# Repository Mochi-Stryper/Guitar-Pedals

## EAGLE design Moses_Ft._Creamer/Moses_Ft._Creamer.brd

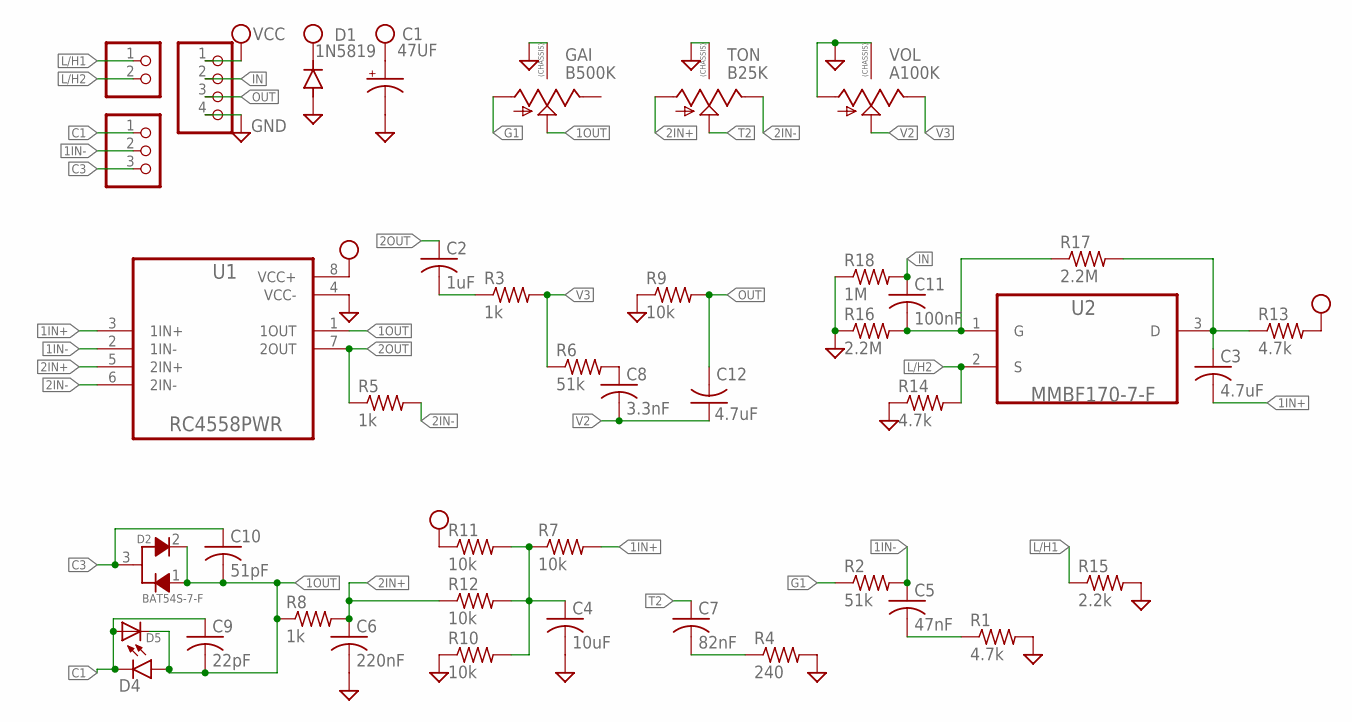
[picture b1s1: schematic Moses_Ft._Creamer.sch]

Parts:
C1: 47UF; PAN_B_SMD+THRU
C2: 1uF; C0805
C3, C12: 4.7uF; C1206
C4: 10uF; C1206
C5: 47nF; C0603
C6: 220nF; C0603
C7: 82nF; C0603
C8: 3.3nF; C0603
C9: 22pF; C0603
C10: 51pF; C0603
C11: 100nF; C0603
D1: 1N5819; SOD123
D2: BAT54S-7-F; SOT23-3
D4: LED0603; LED-0603
D5: DIODESOD-123; SOD-123
GAI: B500K; 9MM_SNAP-IN_POT
JP1: PINHD-1X4; 1X04
JP2: PINHD-1X2; 1X02
JP3: PINHD-1X3; 1X03
R1, R13, R14: 4.7k; R0603
R2, R6: 51k; R0603
R3, R5, R8: 1k; R0603
R4: 240; R0603
R7, R9, R10, R11, R12: 10k; R0603
R15: 2.2k; R0603
R16, R17: 2.2M; R0603
R18: 1M; R0603
TON: B25K; 9MM_SNAP-IN_POT
U1: RC4558PWR; SOP65P640X120-8N
U2: MMBF170-7-F; SOT103P240X110-3N
VOL: A100K; 9MM_SNAP-IN_POT

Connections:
1IN+: C3.2, R7.2, U1.3 (1IN+)
1IN-: C5.1, JP3.2, R2.2, U1.2 (1IN-)
1OUT: C9.2, C10.2, D2.1, D2.2, D4.A, D5.C, GAI.2 (S), R8.1, U1.1 (1OUT)
2IN+: C6.1, R8.2, R12.1, TON.1 (A), U1.5 (2IN+)
2IN-: R5.2, TON.3 (E), U1.6 (2IN-)
2OUT: C2.1, R5.1, U1.7 (2OUT)
C1: C9.1, D4.C, D5.A, JP3.1
C3: C10.1, D2.3, JP3.3
G1: GAI.1 (A), R2.1
GND: C1.-, C1.-- (-), C4.2, C6.2, D1.A, GAI.CHASSIS1, GAI.CHASSIS2, JP1.4, R1.2, R4.2, R9.1, R10.1, R14.1, R15.2, R16.1, R18.1, TON.CHASSIS1, TON.CHASSIS2, U1.4 (VCC-), VOL.1 (A), VOL.CHASSIS1, VOL.CHASSIS2
IN: C11.1, JP1.2, R18.2
L/H1: JP2.1, R15.1
L/H2: JP2.2, R14.2, U2.2 (S)
unnamed: C11.2, R16.2, R17.1, U2.1 (G)
unnamed: C3.1, R13.1, R17.2, U2.3 (D)
unnamed: C5.2, R1.1
unnamed: C4.1, R7.1, R10.2, R11.2, R12.2
unnamed: C2.2, R3.1
unnamed: C7.2, R4.1
unnamed: C8.1, R6.2
OUT: C12.2, JP1.3, R9.2
T2: C7.1, TON.2 (S)
V2: C8.2, C12.1, VOL.2 (S)
V3: R3.2, R6.1, VOL.3 (E)
VCC: C1.+, C1.++ (+), D1.C, JP1.1, R11.1, R13.2, U1.8 (VCC+)

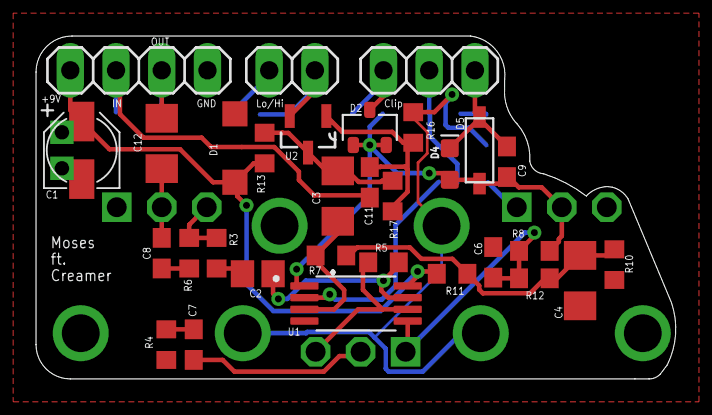
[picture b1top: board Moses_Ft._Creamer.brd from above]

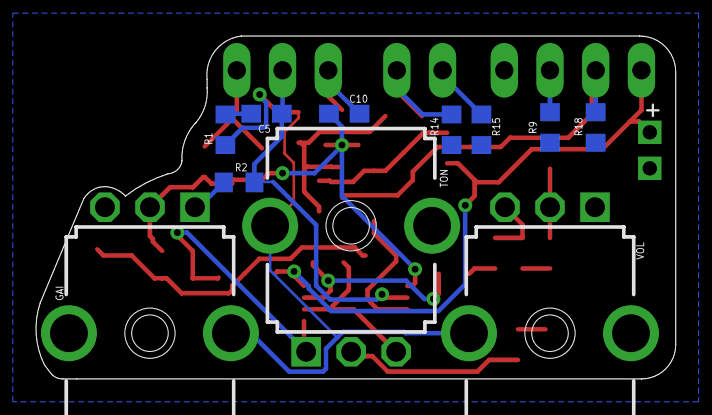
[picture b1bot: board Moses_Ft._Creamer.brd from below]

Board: 2 copper layers, 35.5 x 19.1 mm, 42 parts (11 on the bottom side), 25 nets.

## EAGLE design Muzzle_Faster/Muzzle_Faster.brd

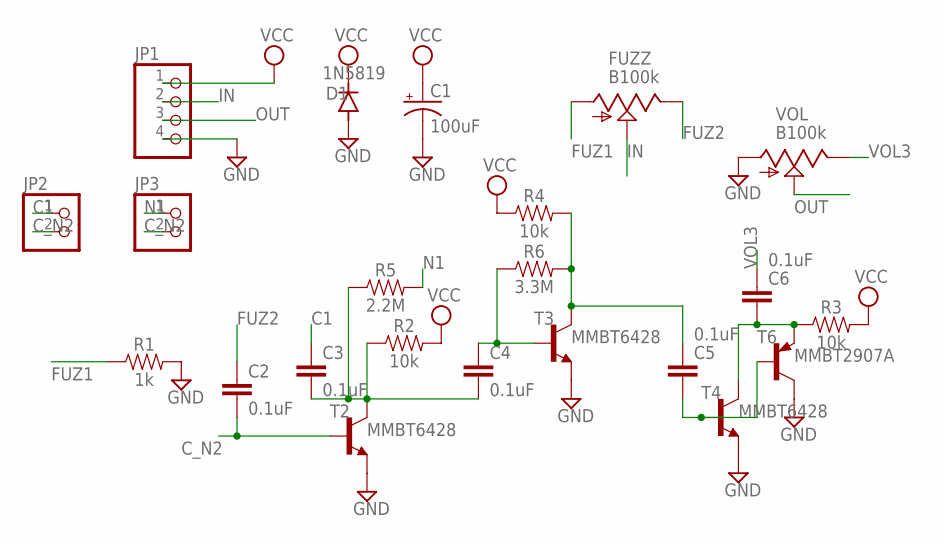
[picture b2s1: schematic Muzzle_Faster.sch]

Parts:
C1: 100uF; PAN_B_SMD+THRU
C2, C3, C4, C5, C6: 0.1uF; 0603
D1: 1N5819; SOD123
FUZZ: B100k; 9MM_SNAP-IN_POT
JP1: PINHD-1X4; 1X04
JP2, JP3: PINHD-1X2; 1X02
R1: 1k; 0603
R2, R3, R4: 10k; 0603
R5: 2.2M; 0603
R6: 3.3M; 0603
T2, T3, T4: MMBT6428; SOT23-BEC
T6: MMBT2907A; SOT23-BEC
VOL: B100k; 9MM_SNAP-IN_POT

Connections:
C1: C3.1, JP2.1
C_N2: C2.2, JP2.2, JP3.2, T2.B
FUZ1: FUZZ.1 (A), R1.1
FUZ2: C2.1, FUZZ.3 (E)
GND: C1.-, C1.-- (-), D1.A, JP1.4, R1.2, T2.E, T3.E, T4.E, T6.C, VOL.1 (A)
IN: FUZZ.2 (S), JP1.2
N1: JP3.1, R5.2
unnamed: C3.2, C4.2, R2.1, R5.1, T2.C
unnamed: C4.1, R6.1, T3.B
unnamed: C5.1, R4.2, R6.2, T3.C
unnamed: C5.2, T4.B, T6.B
unnamed: C6.2, R3.1, T4.C, T6.E
OUT: JP1.3, VOL.2 (S)
VCC: C1.+, C1.++ (+), D1.C, JP1.1, R2.2, R3.2, R4.1
VOL3: C6.1, VOL.3 (E)

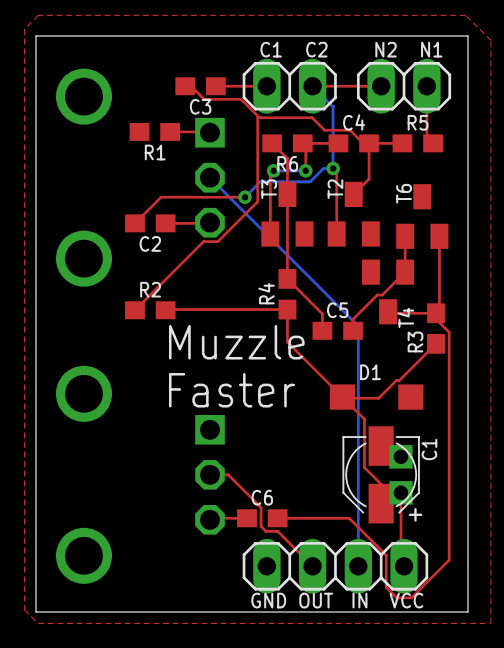
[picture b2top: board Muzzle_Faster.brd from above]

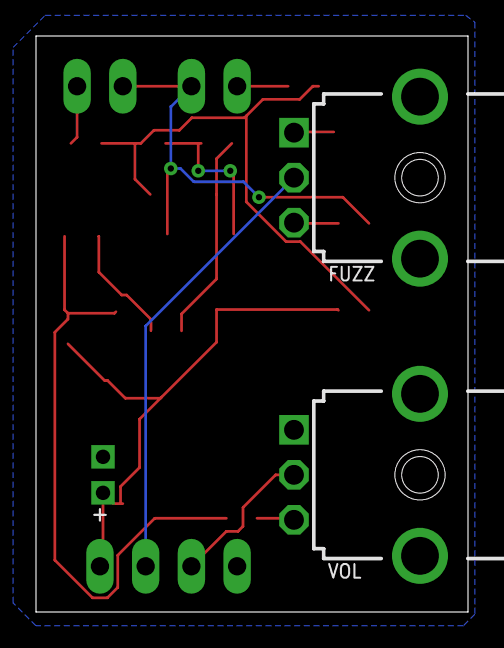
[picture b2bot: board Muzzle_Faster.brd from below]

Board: 2 copper layers, 24.0 x 32.0 mm, 22 parts (2 on the bottom side), 15 nets.

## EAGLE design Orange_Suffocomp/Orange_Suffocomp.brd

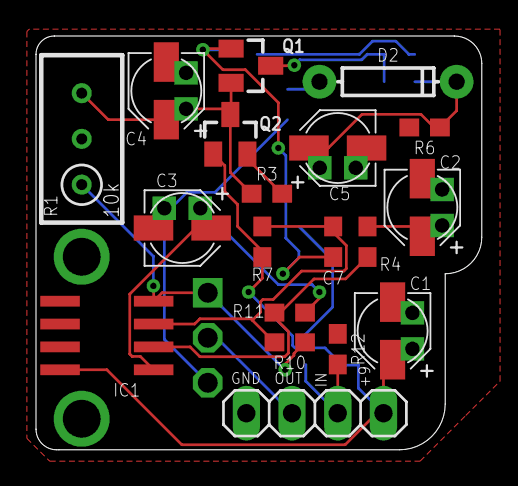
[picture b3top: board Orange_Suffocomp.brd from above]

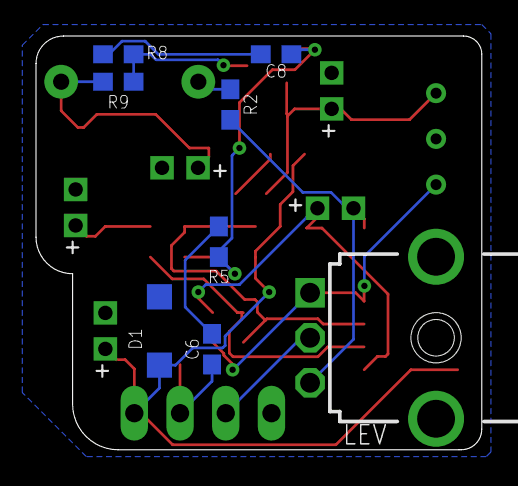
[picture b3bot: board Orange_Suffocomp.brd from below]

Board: 2 copper layers, 24.8 x 23.0 mm, 27 parts (8 on the bottom side), 17 nets.

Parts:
C1: 100uF; PAN_B_SMD+THRU
C2, C3, C4, C5: 4.7uF; PAN_B_SMD+THRU
C6, C7: 47nF; 0603
C8: 2.2nF; 0603
D1: 1N5819; SOD123
D2: 1n34a; DIODE-1N4148
IC1: LM4558D; SO08
JP1: 1X04
LEV: A10k; 9MM_SNAP-IN_POT
Q1, Q2: MMBF5457; SOT23
R1: 10k; RTRIM3296W
R2: 1.5k; 0603
R3: 2.4k; 0603
R4: 10k; 0603
R5: 82k; 0603
R6: 100k; 0603
R7: 390k; 0603
R8, R9, R10: 470k; 0603
R11: 220k; 0603
R12: 4.7M; 0603

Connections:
GND: C1.-, C1.--, C2.-, C2.--, C4.-, C4.--, C5.-, C5.--, D1.A, IC1.4, JP1.4, LEV.1, R1.1, R1.2, R6.2, R10.1, R12.1
IN: C6.1, JP1.2, R12.2
LEV3: C3.-, C3.--, LEV.3, R2.2
unnamed: C6.2, R5.1
unnamed: C7.1, C8.2, Q1.1, R5.2
unnamed: C7.2, IC1.3, R7.1, R10.2
unnamed: C8.1, R8.1
unnamed: C2.+, C2.++, R4.2
unnamed: IC1.2, R4.1, R11.1
unnamed: C3.+, C3.++, IC1.1, R11.2
unnamed: Q1.3, R8.2, R9.1
unnamed: C4.+, C4.++, Q1.2, Q2.3, R1.3, R3.1
unnamed: Q2.2, R3.2
unnamed: C5.+, C5.++, D2.C, R6.1, R9.2
unnamed: D2.A, R2.1
OUT: JP1.3, LEV.2
VCC: C1.+, C1.++, D1.C, IC1.8, JP1.1, Q2.1, R7.2

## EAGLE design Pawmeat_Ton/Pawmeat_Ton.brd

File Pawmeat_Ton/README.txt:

~Incomplete~
~Halted due to concerns over breaching components' current rating~
Electrosmash 1Wamp Clone
R-C & C-R filter values altered

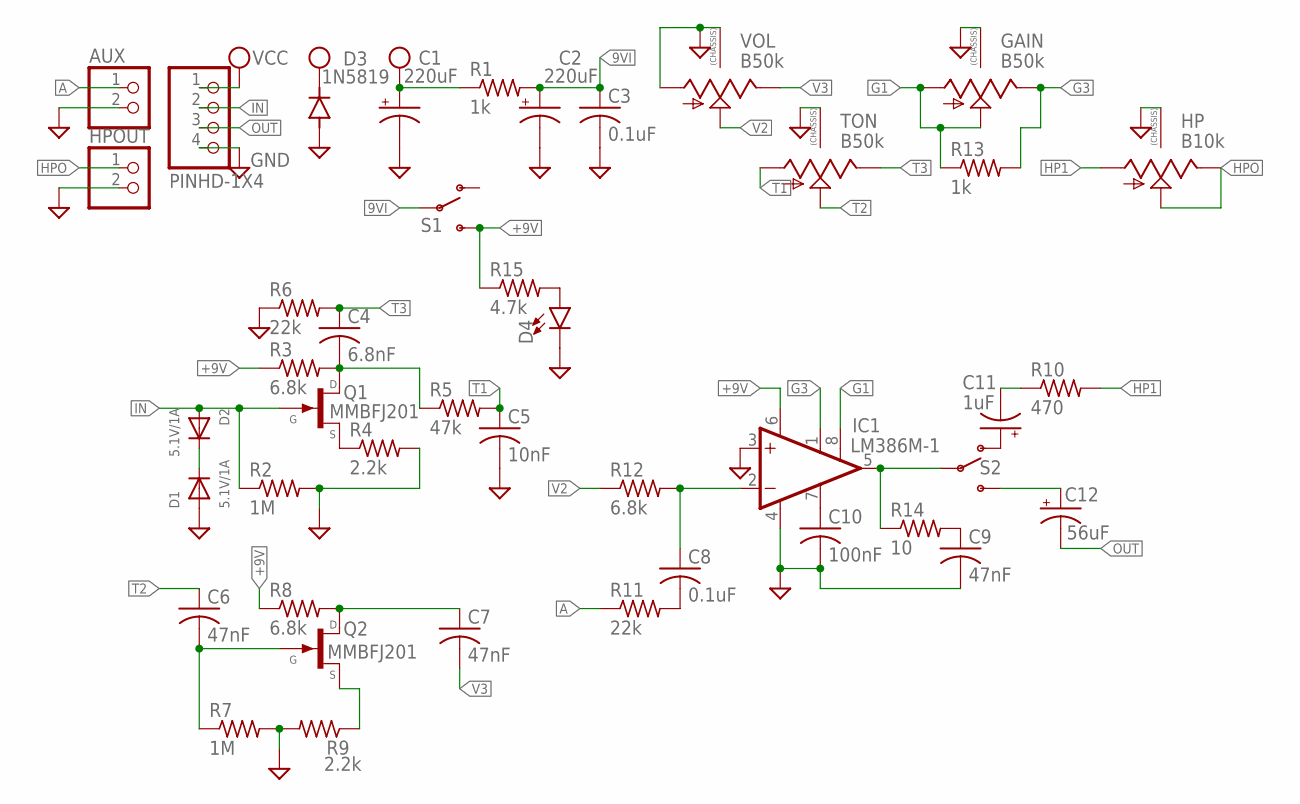
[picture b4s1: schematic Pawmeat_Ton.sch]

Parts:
AUX: PINHD-1X2; 1X02
C1, C2: 220uF; PAN_B_SMD+THRU
C3, C8: 0.1uF; C0402
C4: 6.8nF; C0402
C5: 10nF; C0402
C6, C7, C9: 47nF; C0402
C10: 100nF; C0402
C11: 1uF; PAN_B_SMD+THRU
C12: 56uF; PAN_B_SMD+THRU
D1, D2: 5.1V/1A; SMADIODE
D3: 1N5819; SOD123
D4: LED0603; LED-0603
GAIN: B50k; 9MM_SNAP-IN_POT
HP: B10k; 9MM_SNAP-IN_POT
HPOUT: PINHD-1X2; 1X02
IC1: LM386M-1; SO08
JP1: PINHD-1X4; 1X04
Q1, Q2: MMBFJ201; SOT23
R1, R13: 1k; R0402
R2, R7: 1M; R0402
R3, R8, R12: 6.8k; R0402
R4, R9: 2.2k; R0402
R5: 47k; R0402
R6, R11: 22k; R0402
R10: 470; R0402
R14: 10; R0402
R15: 4.7k; R0402
S1, S2: SWITCH-SPDTSMD2; SWITCH-SPDT-SMD
TON: B50k; 9MM_SNAP-IN_POT
VOL: B50k; 9MM_SNAP-IN_POT

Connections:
9VI: C2.+, C2.++ (+), C3.1, R1.2, S1.2
+9V: IC1.6 (VS), R3.1, R8.1, R15.1, S1.3 (S)
A: AUX.1, R11.1
G1: GAIN.1 (A), GAIN.2 (S), IC1.8 (GAIN), R13.1
G3: GAIN.3 (E), IC1.1 (GAIN), R13.2
GND: AUX.2, C1.-, C1.-- (-), C2.-, C2.-- (-), C3.2, C5.2, C9.2, C10.2, D1.A, D3.A, D4.C, GAIN.CHASSIS1, GAIN.CHASSIS2, HP.CHASSIS1, HP.CHASSIS2, HPOUT.2, IC1.3 (+IN), IC1.4 (GND), JP1.4, R2.2, R4.2, R6.1, R7.2, R9.2, TON.CHASSIS1, TON.CHASSIS2, VOL.1 (A), VOL.CHASSIS1, VOL.CHASSIS2
HP1: HP.1 (A), R10.2
HPO: HP.2 (S), HP.3 (E), HPOUT.1
IN: D2.A, JP1.2, Q1.3 (G), R2.1
unnamed: C4.2, Q1.1 (D), R3.2, R5.1
unnamed: D1.C, D2.C
unnamed: Q1.2 (S), R4.1
unnamed: C6.2, Q2.3 (G), R7.1
unnamed: Q2.2 (S), R9.1
unnamed: C7.1, Q2.1 (D), R8.2
unnamed: C8.2, R11.2
unnamed: C8.1, IC1.2 (-IN), R12.2
unnamed: C10.1, IC1.7 (BYPASS)
unnamed: C9.1, R14.2
unnamed: C12.+, C12.++ (+), S2.3 (S)
unnamed: IC1.5 (OUT), R14.1, S2.2
unnamed: C11.+, C11.++ (+), S2.1 (O)
unnamed: C11.-, C11.-- (-), R10.1
unnamed: D4.A, R15.2
OUT: C12.-, C12.-- (-), JP1.3
T1: C5.1, R5.2, TON.1 (A)
T2: C6.1, TON.2 (S)
T3: C4.1, R6.2, TON.3 (E)
V2: R12.1, VOL.2 (S)
V3: C7.2, VOL.3 (E)
VCC: C1.+, C1.++ (+), D3.C, JP1.1, R1.1

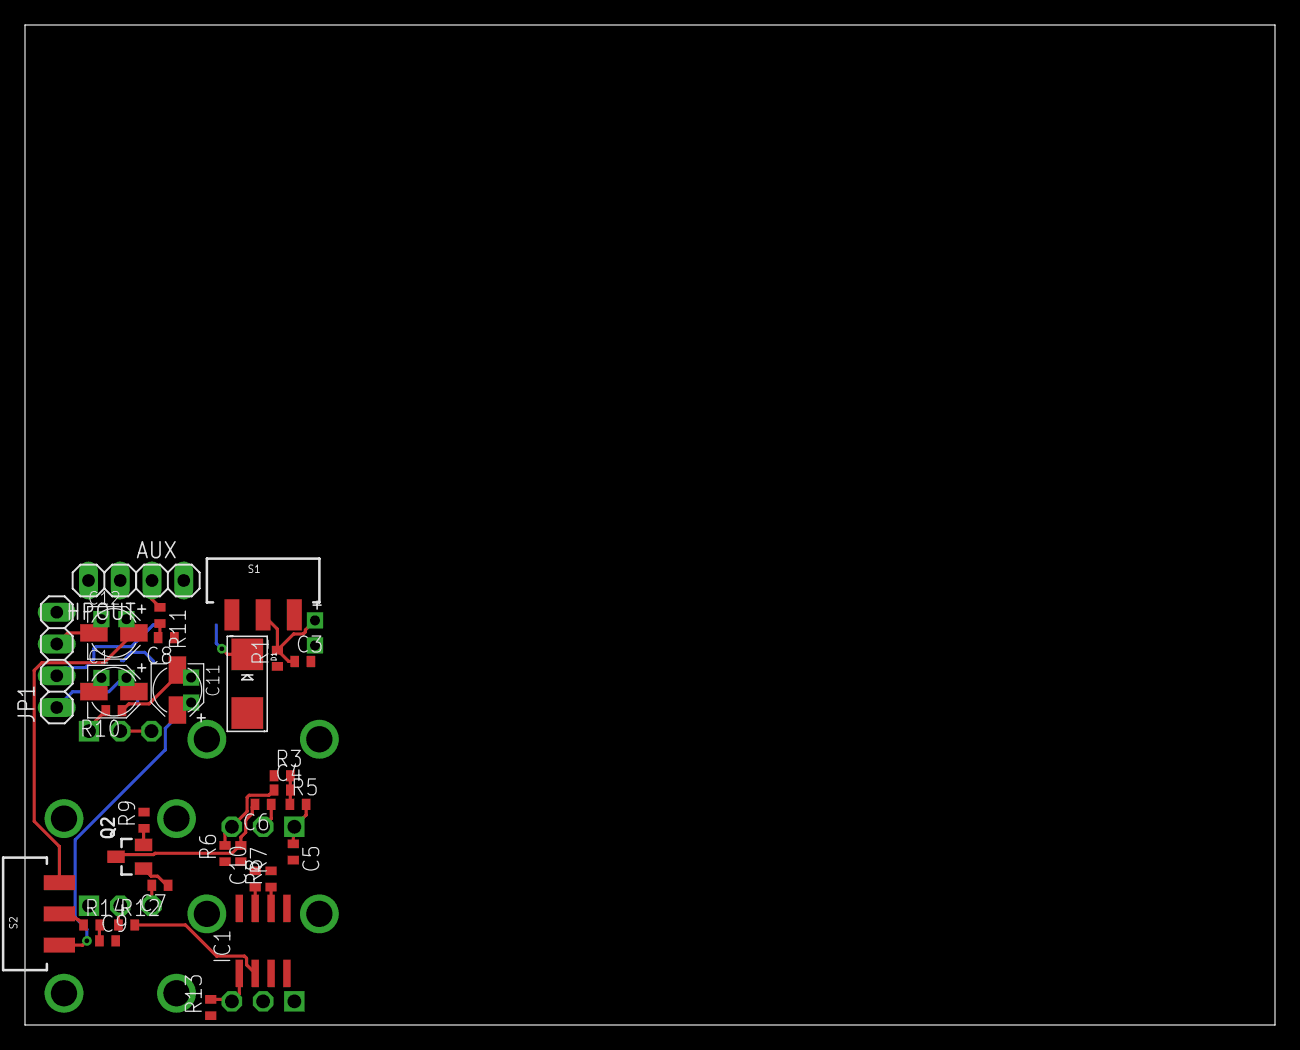
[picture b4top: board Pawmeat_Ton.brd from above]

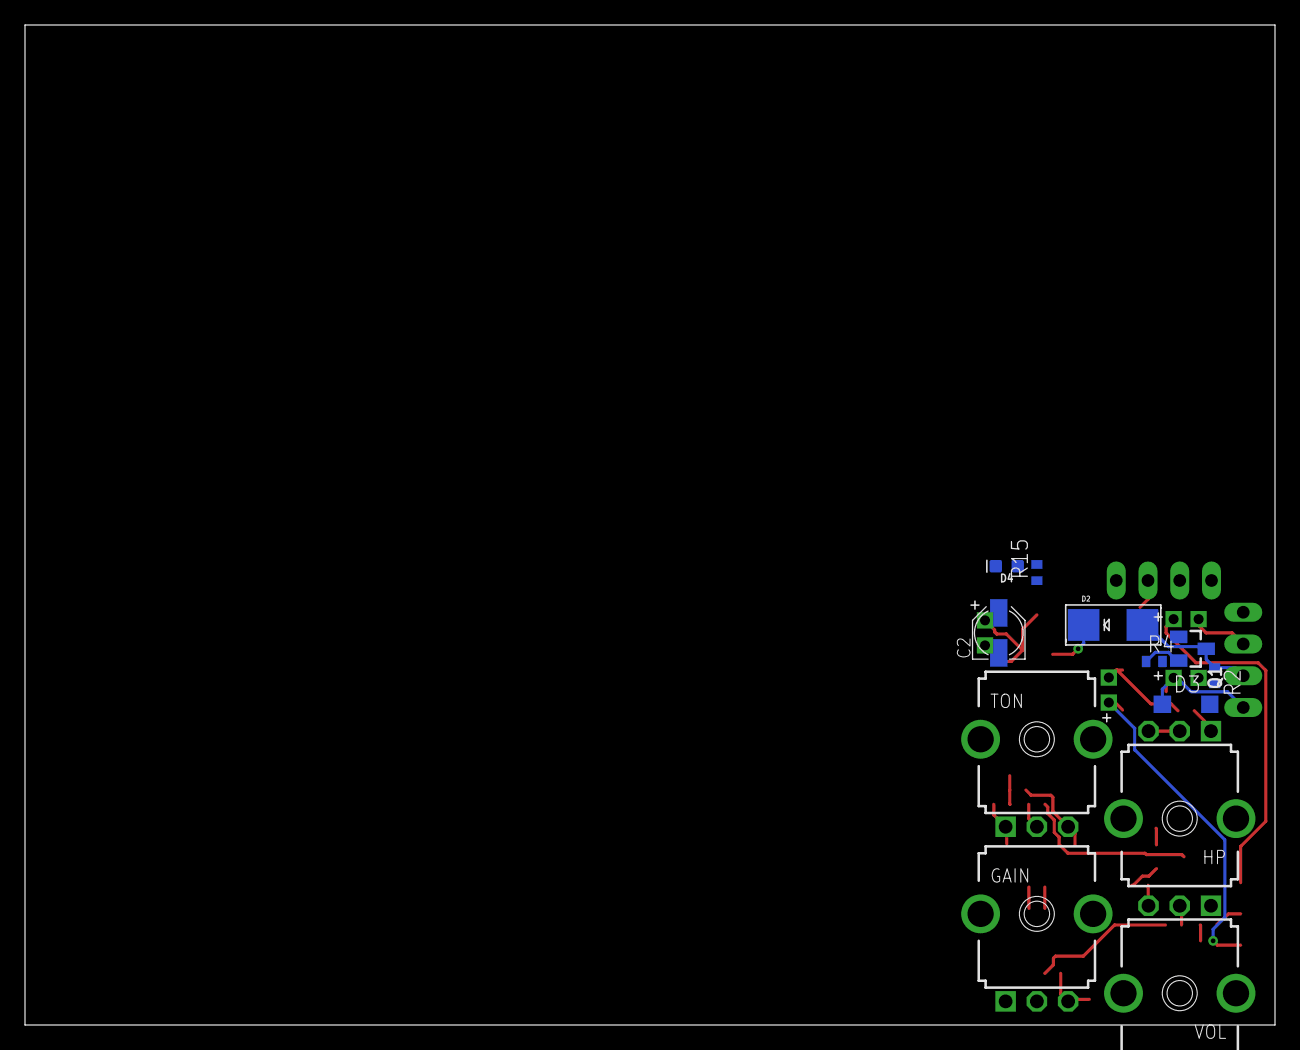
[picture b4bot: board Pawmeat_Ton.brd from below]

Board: 2 copper layers, 100.0 x 80.0 mm, 43 parts (12 on the bottom side), 31 nets.

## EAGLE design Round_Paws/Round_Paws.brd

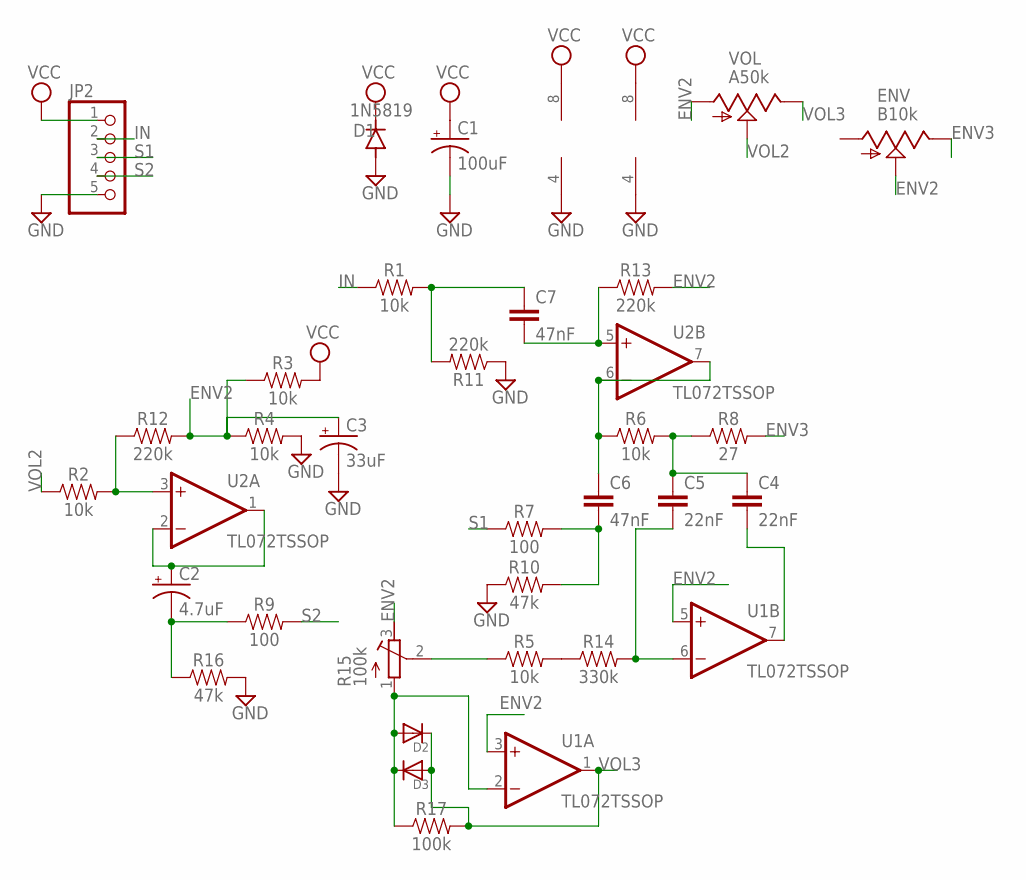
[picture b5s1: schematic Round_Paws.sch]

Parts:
C1: 100uF; PAN_B_SMD+THRU
C2: 4.7uF; PAN_B_SMD+THRU
C3: 33uF; PAN_B_SMD+THRU
C4, C5: 22nF; 0603
C6, C7: 47nF; 0603
D1: 1N5819; SOD123
D2, D3: DIODESOD-123; SOD-123
ENV: B10k; 9MM_SNAP-IN_POT
JP2: PINHD-1X5; 1X05
R1, R2, R3, R4, R5, R6: 10k; 0603
R7, R9: 100; 0603
R8: 27; 0603
R10, R16: 47k; 0603
R11, R12, R13: 220k; 0603
R14: 330k; 0603
R15: 100k; RTRIM3296W
R17: 100k; 0603
U1, U2: TL072TSSOP; TSSOP-8
VOL: A50k; 9MM_SNAP-IN_POT

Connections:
ENV2: C3.+, C3.++ (+), ENV.2 (S), R3.1, R4.1, R12.2, R13.2, R15.3 (E), U1.3 (+IN), U1.5 (+IN), VOL.1 (A)
ENV3: ENV.3 (E), R8.2
GND: C1.-, C1.-- (-), C3.-, C3.-- (-), D1.A, JP2.5, R4.2, R10.1, R11.1, R16.2, U1.4 (V-), U2.4 (V-)
IN: JP2.2, R1.1
unnamed: C7.1, R1.2, R11.2
unnamed: C7.2, R13.1, U2.5 (+IN)
unnamed: C6.1, R6.1, U2.6 (-IN), U2.7 (OUT)
unnamed: C4.1, C5.1, R6.2, R8.1
unnamed: C6.2, R7.2, R10.2
unnamed: C5.2, R14.2, U1.6 (-IN)
unnamed: R5.2, R14.1
unnamed: R5.1, R15.2 (S)
unnamed: D2.A, D3.C, R15.1 (A), R17.1, U1.2 (-IN)
unnamed: C4.2, U1.7 (OUT)
unnamed: R2.2, R12.1, U2.3 (+IN)
unnamed: C2.+, C2.++ (+), U2.1 (OUT), U2.2 (-IN)
unnamed: C2.-, C2.-- (-), R9.1, R16.1
S1: JP2.3, R7.1
S2: JP2.4, R9.2
VCC: C1.+, C1.++ (+), D1.C, JP2.1, R3.2, U1.8 (V+), U2.8 (V+)
VOL2: R2.1, VOL.2 (S)
VOL3: D2.C, D3.A, R17.2, U1.1 (OUT), VOL.3 (E)

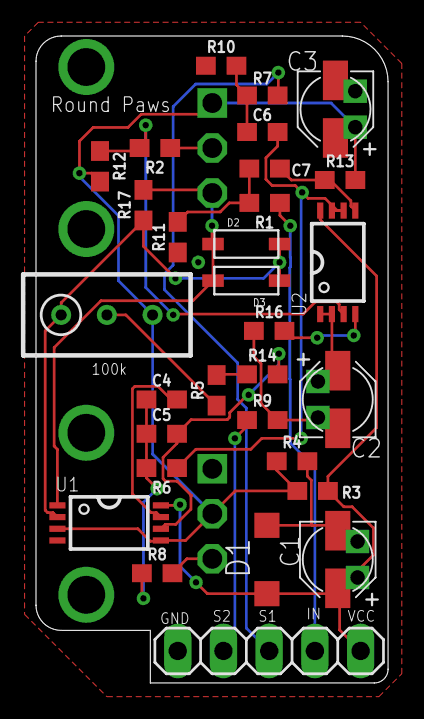
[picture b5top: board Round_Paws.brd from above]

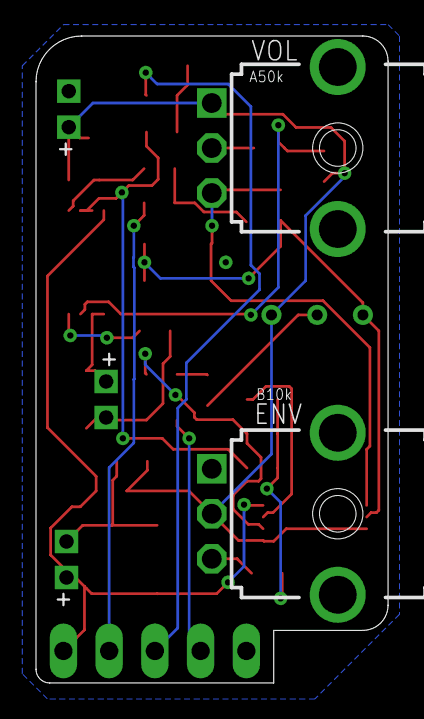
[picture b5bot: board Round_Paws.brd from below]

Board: 2 copper layers, 19.6 x 35.9 mm, 32 parts (2 on the bottom side), 22 nets.

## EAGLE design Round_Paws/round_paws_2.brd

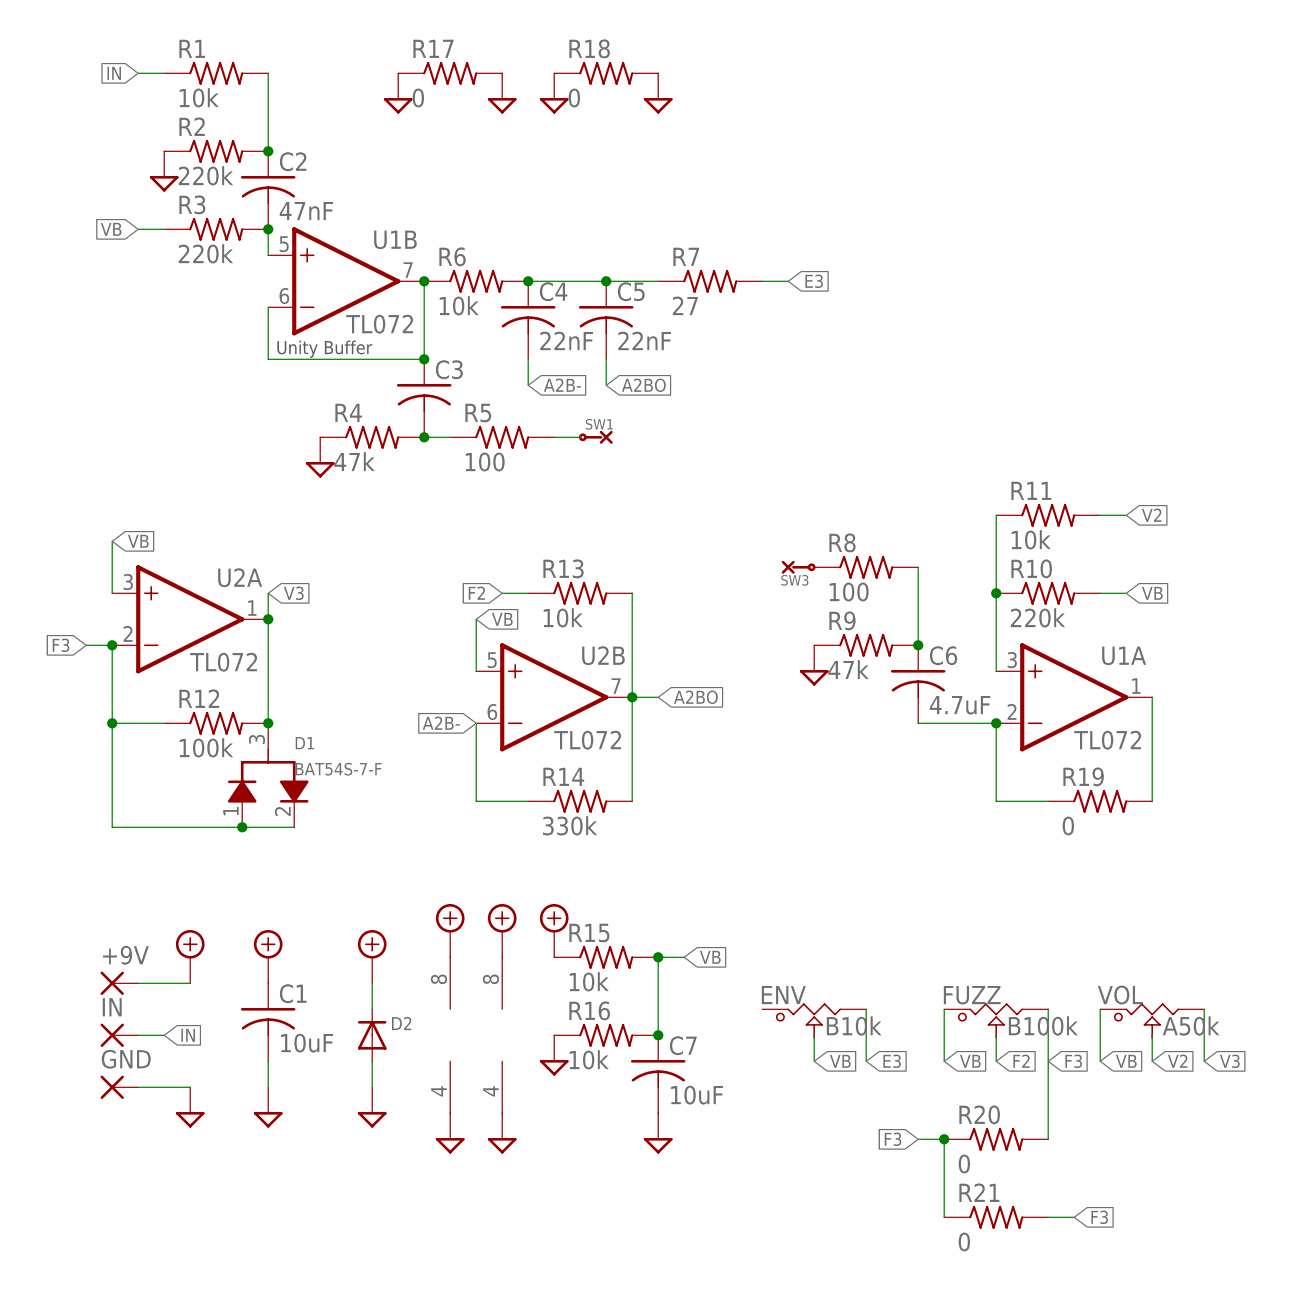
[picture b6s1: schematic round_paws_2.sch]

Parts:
+9V: SMD2; SMD1,27-2,54
C1, C7: 10uF; C1206
C2: 47nF; C0603
C3: C-USC0603; C0603
C4, C5: 22nF; C0603
C6: 4.7uF; C1206
D1: BAT54S-7-F; SOT23-3
D2: DIODESOD-123; SOD-123
ENV: B10k; POT_9MM_SMD
FUZZ: B100k; POT_9MM_SMD
GND: SMD2; SMD1,27-2,54
IN: SMD2; SMD1,27-2,54
R1, R6, R11, R13, R15, R16: 10k; R0603
R2, R3, R10: 220k; R0603
R4, R9: 47k; R0603
R5, R8: 100; R0603
R7: 27; R0603
R12: 100k; R0603
R14: 330k; R0603
R17, R18, R19, R20, R21: 0; R0402
SW1, SW3: COM_SMD; 1PAD
U1, U2: TL072; TSSOP-8
VOL: A50k; POT_9MM_SMD

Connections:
1B+: C2.2, R3.2, U1.5 (+IN)
+9V: +9V.1, C1.1, D2.C, R15.1, U1.8 (V+), U2.8 (V+)
A1A+: R10.1, R11.1, U1.3 (+IN)
A1AO: C6.2, R19.1, R19.2, U1.1 (OUT), U1.2 (-IN)
A1BO: C3.1, R6.1, U1.6 (-IN), U1.7 (OUT)
A2B-: C4.2, R14.1, U2.6 (-IN)
A2BO: C5.2, R13.2, R14.2, U2.7 (OUT)
E3: ENV.3, R7.2
F2: FUZZ.2, R13.1
F3: D1.1, D1.2, FUZZ.3, R12.1, R20.1, R20.2, R21.1, R21.2, U2.2 (-IN)
GND: C1.2, C7.2, D2.A, GND.1, R2.1, R4.1, R9.1, R16.1, R17.1, R17.2, R18.1, R18.2, U1.4 (V-), U2.4 (V-)
IN: IN.1, R1.1
unnamed: C2.1, R1.2, R2.2
unnamed: C6.1, R8.2, R9.2
unnamed: R8.1, SW3.1
unnamed: C3.2, R4.2, R5.1
unnamed: R5.2, SW1.1
unnamed: C4.1, C5.1, R6.2, R7.1
V2: R11.2, VOL.2
V3: D1.3, R12.2, U2.1 (OUT), VOL.3
VB: C7.1, ENV.2, FUZZ.1, R3.1, R10.2, R15.2, R16.2, U2.3 (+IN), U2.5 (+IN), VOL.1

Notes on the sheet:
Unity Buffer

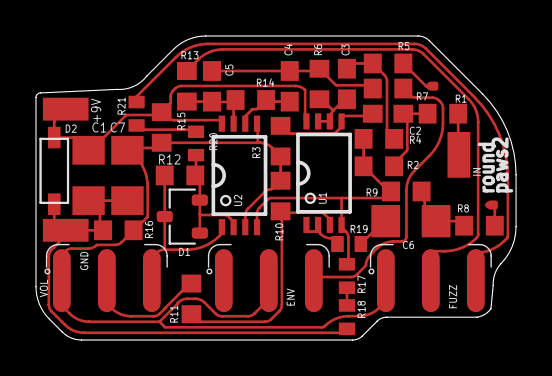
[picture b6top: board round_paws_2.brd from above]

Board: 2 copper layers, 26.7 x 16.9 mm, 40 parts (0 on the bottom side), 21 nets.

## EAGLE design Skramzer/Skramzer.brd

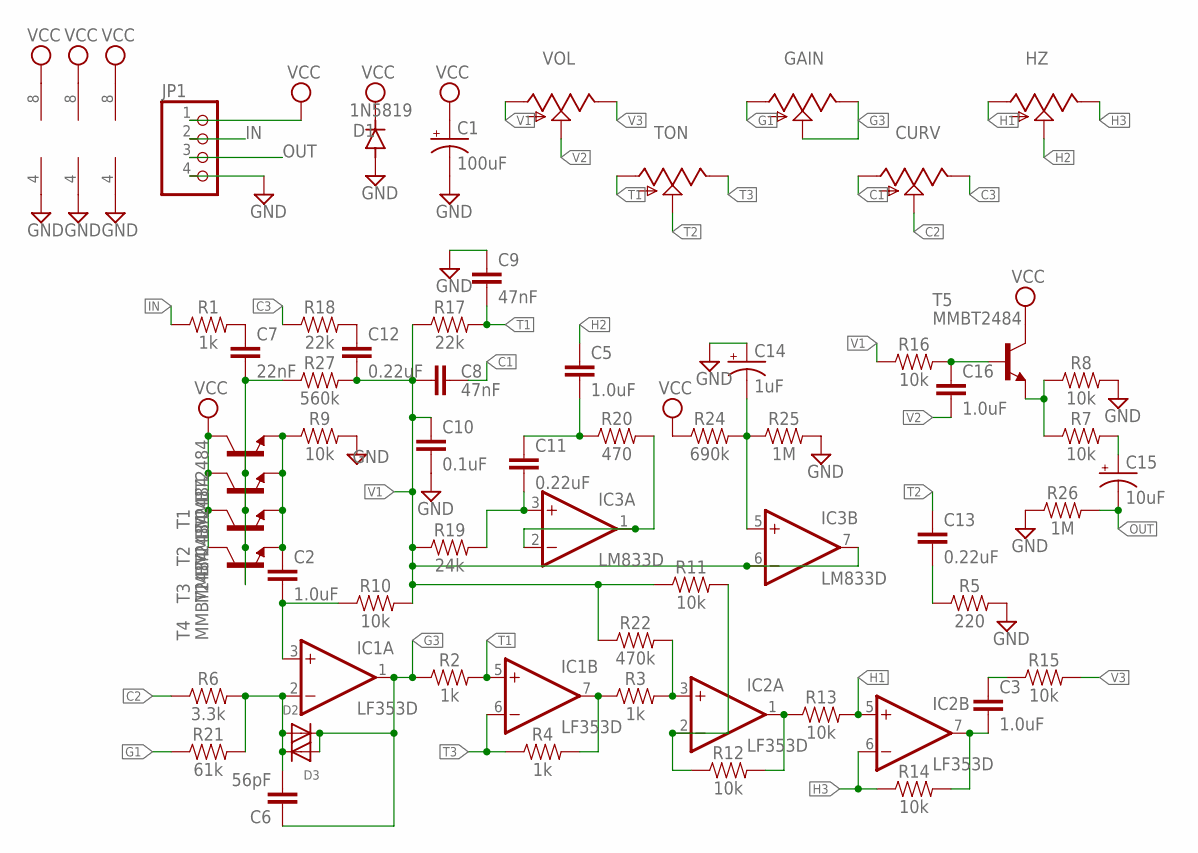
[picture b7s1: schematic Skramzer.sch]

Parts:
C1: 100uF; PAN_B_SMD+THRU
C2, C3, C5, C16: 1.0uF; 0603
C6: 56pF; 0603
C7: 22nF; 0603
C8, C9: 47nF; 0603
C10: 0.1uF; 0603
C11, C12, C13: 0.22uF; 0603
C14: 1uF; PAN_B_SMD+THRU
C15: 10uF; PAN_B_SMD+THRU
CURV: 9MM_SNAP-IN_POT_; 9MM_SNAP-IN_POT
D1: 1N5819; SOD123
D2, D3: DIODESOD-123; SOD-123
GAIN: 9MM_SNAP-IN_POT_; 9MM_SNAP-IN_POT
HZ: 9MM_SNAP-IN_POT_; 9MM_SNAP-IN_POT
IC1, IC2: LF353D; SO08
IC3: LM833D; SO08
JP1: PINHD-1X4; 1X04
R1, R2, R3, R4: 1k; 0603
R5: 220; 0603
R6: 3.3k; 0603
R7, R8, R9, R10, R11, R12, R13, R14, R15, R16: 10k; 0603
R17, R18: 22k; 0603
R19: 24k; 0603
R20: 470; 0603
R21: 61k; 0603
R22: 470k; 0603
R24: 690k; 0603
R25, R26: 1M; 0603
R27: 560k; 0603
T1, T2, T3, T4, T5: MMBT2484; SOT23-BEC
TON: 9MM_SNAP-IN_POT_; 9MM_SNAP-IN_POT
VOL: 9MM_SNAP-IN_POT_; 9MM_SNAP-IN_POT

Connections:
C1: C8.1, CURV.1 (A)
C2: CURV.2 (S), R6.1
C3: CURV.3 (E), R18.1
G1: GAIN.1 (A), R21.1
G3: C6.1, D2.C, D3.A, GAIN.2 (S), GAIN.3 (E), IC1.1 (OUT), R2.1
GND: C1.-, C1.-- (-), C9.1, C10.2, C14.+, C14.++ (+), D1.A, IC1.4 (V-), IC2.4 (V-), IC3.4 (V-), JP1.4, R5.2, R8.2, R9.2, R25.2, R26.1
H1: HZ.1 (A), IC2.5 (+IN), R13.2
H2: C5.1, HZ.2 (S)
H3: HZ.3 (E), IC2.6 (-IN), R14.1
IN: JP1.2, R1.1
unnamed: C7.2, R27.1, T1.B, T2.B, T3.B, T4.B
unnamed: C7.1, R1.2
unnamed: C2.1, R9.1, T1.E, T2.E, T3.E, T4.E
unnamed: C2.2, IC1.3 (+IN), R10.1
unnamed: C14.-, C14.-- (-), IC3.5 (+IN), R24.2, R25.1
unnamed: C12.1, R18.2
unnamed: C6.2, D2.A, D3.C, IC1.2 (-IN), R6.2, R21.2
unnamed: IC2.3 (+IN), R3.2, R22.2
unnamed: IC1.7 (OUT), R3.1, R4.2
unnamed: IC2.2 (-IN), R11.2, R12.1
unnamed: IC2.1 (OUT), R12.2, R13.1
unnamed: C3.1, R15.1
unnamed: C3.2, IC2.7 (OUT), R14.2
unnamed: C16.1, R16.2, T5.B
unnamed: C11.2, IC3.3 (+IN), R19.2
unnamed: IC3.1 (OUT), IC3.2 (-IN), R20.2
unnamed: C5.2, C11.1, R20.1
unnamed: C15.+, C15.++ (+), R7.2
unnamed: R7.1, R8.1, T5.E
unnamed: C13.2, R5.1
OUT: C15.-, C15.-- (-), JP1.3, R26.2
T1: C9.2, IC1.5 (+IN), R2.2, R17.2, TON.1 (A)
T2: C13.1, TON.2 (S)
T3: IC1.6 (-IN), R4.1, TON.3 (E)
V1: C8.2, C10.1, C12.2, IC3.6 (-IN), IC3.7 (OUT), R10.2, R11.1, R16.1, R17.1, R19.1, R22.1, R27.2, VOL.1 (A)
V2: C16.2, VOL.2 (S)
V3: R15.2, VOL.3 (E)
VCC: C1.+, C1.++ (+), D1.C, IC1.8 (V+), IC2.8 (V+), IC3.8 (V+), JP1.1, R24.1, T1.C, T2.C, T3.C, T4.C, T5.C

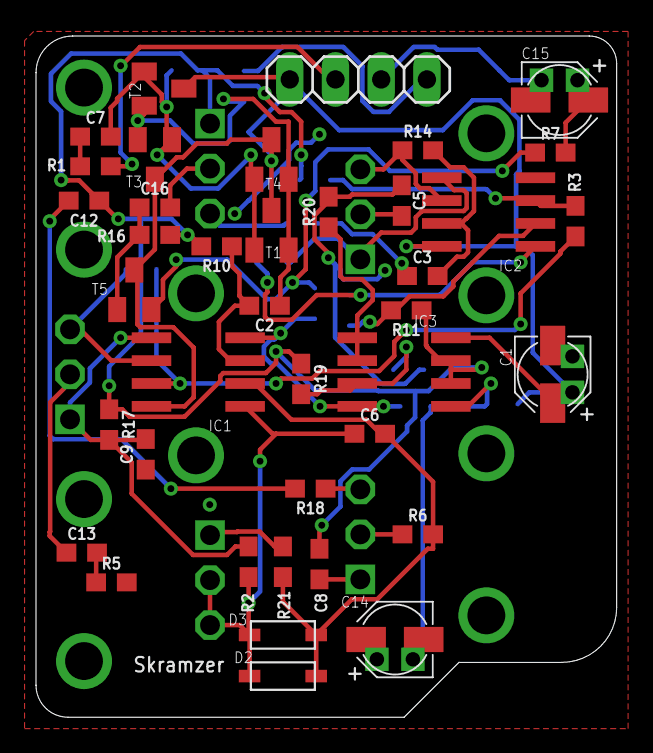
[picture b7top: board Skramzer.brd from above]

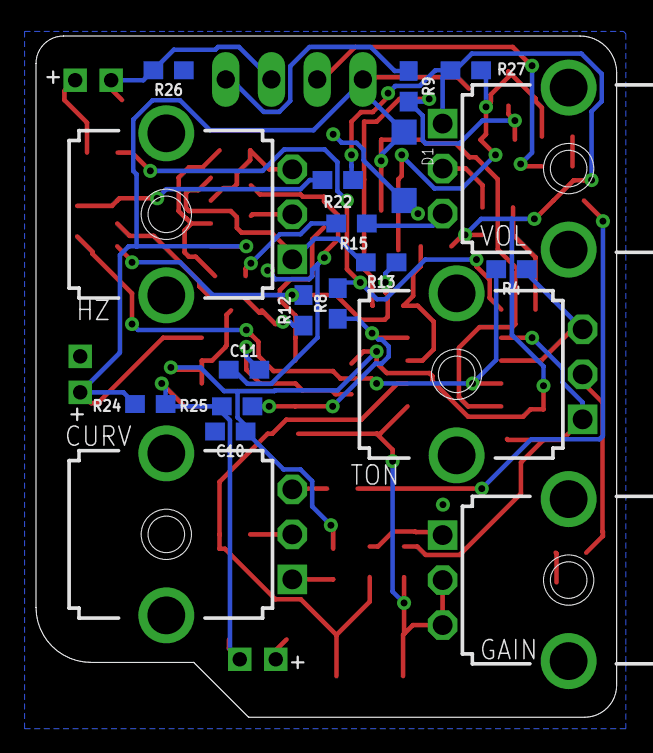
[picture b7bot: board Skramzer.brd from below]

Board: 2 copper layers, 32.3 x 37.8 mm, 58 parts (19 on the bottom side), 38 nets.

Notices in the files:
parts and their libraries:
SparkFun-LED: Licensing: Creative Commons ShareAlike 4.0 International - https://creativecommons.org/licenses/by-sa/4.0
